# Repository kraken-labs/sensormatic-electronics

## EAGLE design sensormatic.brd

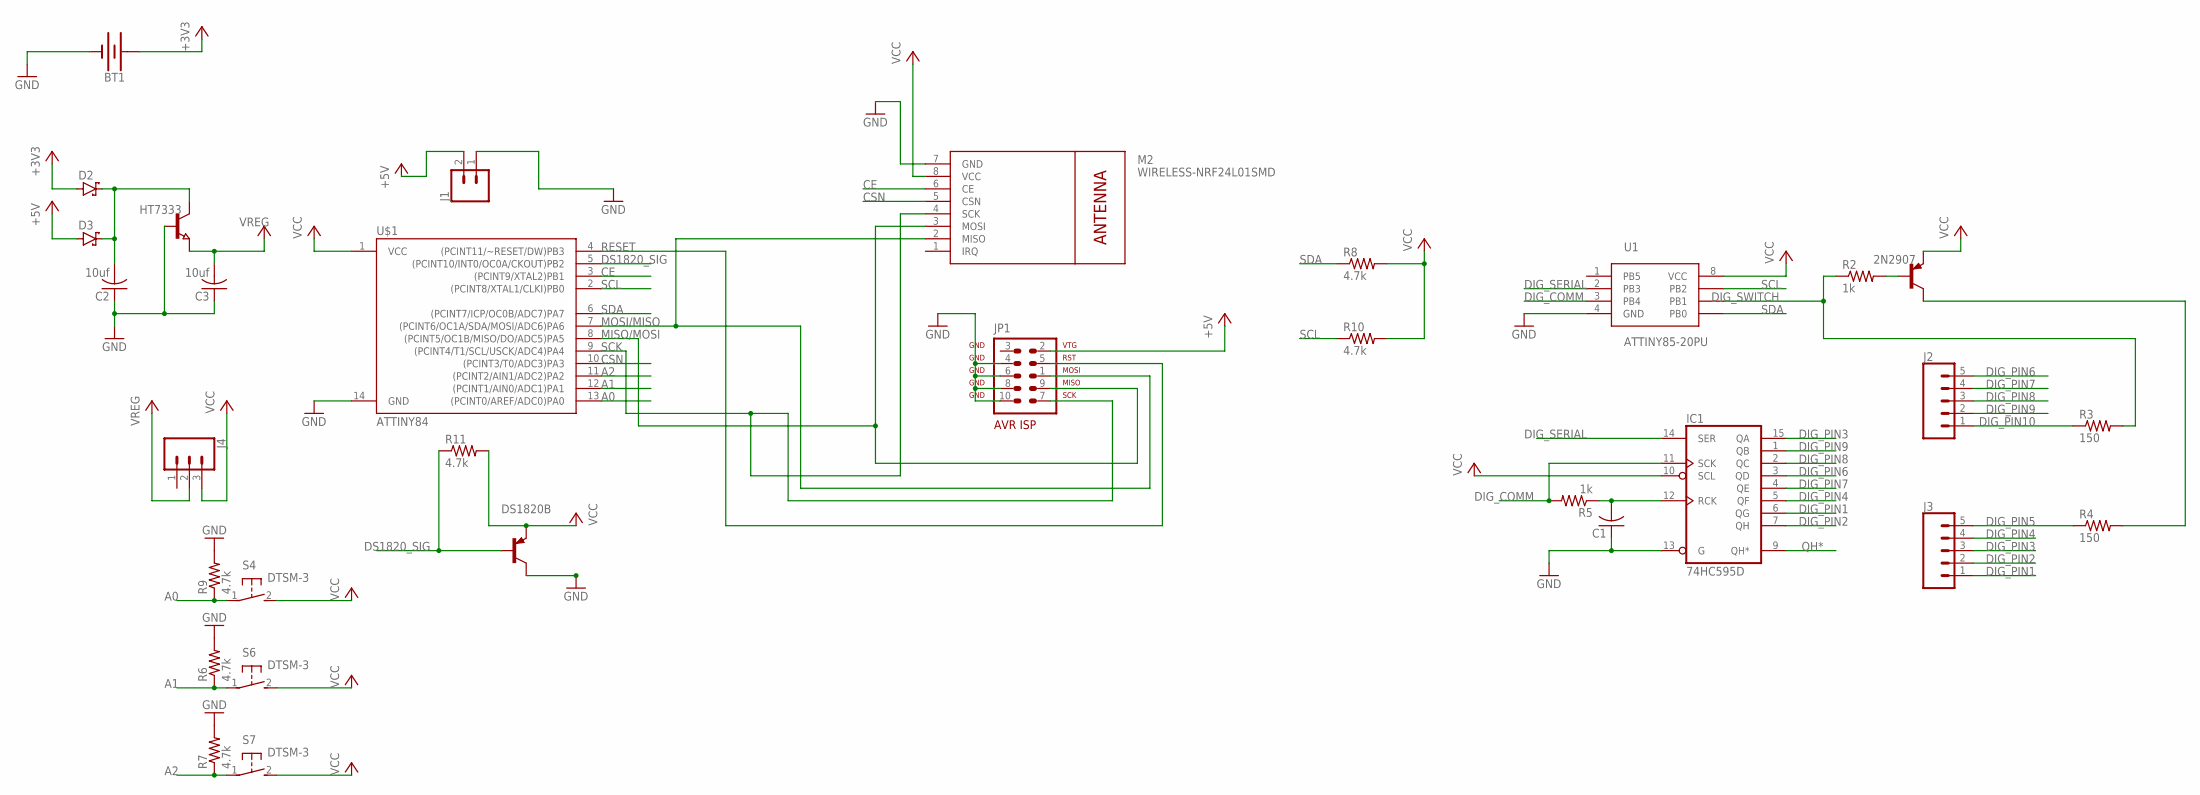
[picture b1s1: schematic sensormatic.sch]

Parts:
2N2907: BCX71SMD; SOT23
BT1: BATTERY-20MM_PTH; BATTCOM_20MM_PTH
C1: C-USC0603; C0603
C2, C3: 10uf; C0603
D2, D3: SCHOTTKY-DIODESMD; SMB
DS1820B: -PNP-TO92; TO92
HT7333: NPN-TRANSISTOR_SOT89; SOT89
IC1: 74HC595D; SO16
J1: CONN_02; 1X02
J2, J3: CONN_05NO_SILK; 1X05_NO_SILK
J4: CONN_03; 1X03
JP1: AVR-ISP-10
M2: WIRELESS-NRF24L01SMD; WIRELESS-NRF24L01-SMD
R2, R5: 1k; R0805
R3, R4: 150; R0805
R6, R7, R8, R9, R10, R11: 4.7k; R0805
S4, S6, S7: DTSM-3
U1: ATTINY85-20PU; PDIP-8
U$1: ATTINY84; SO14

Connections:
+3V3: BT1.1 (+), D2.A
+5V: D3.A, J1.2, JP1.2
A0: R9.1, S4.1, U$1.13 ((PCINT0/AREF/ADC0)PA0)
A1: R6.1, S6.1, U$1.12 ((PCINT1/AIN0/ADC1)PA1)
A2: R7.1, S7.1, U$1.11 ((PCINT2/AIN1/ADC2)PA2)
CE: M2.6 (CE), U$1.3 ((PCINT9/XTAL2)PB1)
CSN: M2.5 (CSN), U$1.10 ((PCINT3/T0/ADC3)PA3)
DIG_COMM: IC1.11 (SCK), R5.2, U1.3 (PB4)
DIG_PIN1: IC1.6 (QG), J3.1
DIG_PIN2: IC1.7 (QH), J3.2
DIG_PIN3: IC1.15 (QA), J3.3
DIG_PIN4: IC1.5 (QF), J3.4
DIG_PIN5: J3.5, R4.1
DIG_PIN6: IC1.3 (QD), J2.5
DIG_PIN7: IC1.4 (QE), J2.4
DIG_PIN8: IC1.2 (QC), J2.3
DIG_PIN9: IC1.1 (QB), J2.2
DIG_PIN10: J2.1, R3.1
DIG_SERIAL: IC1.14 (SER), U1.2 (PB3)
DIG_SWITCH: R2.1, R3.2, U1.6 (PB1)
DS1820_SIG: DS1820B.2 (B), R11.1, U$1.5 ((PCINT10/INT0/OC0A/CKOUT)PB2)
GND: BT1.2 (-), C1.1, C2.1, C3.1, DS1820B.3 (C), HT7333.1 (B), IC1.8 (GND), IC1.13 (G), J1.1, JP1.4, JP1.6, JP1.8, JP1.10, M2.7 (GND), R6.2, R7.2, R9.2, U1.4 (GND), U$1.14 (GND)
MISO/MOSI: JP1.9, M2.3 (MOSI), U$1.8 ((PCINT5/OC1B/MISO/DO/ADC5)PA5)
MOSI/MISO: JP1.1, M2.2 (MISO), U$1.7 ((PCINT6/OC1A/SDA/MOSI/ADC6)PA6)
unnamed: C2.2, D2.C, D3.C, HT7333.2 (C)
unnamed: 2N2907.1 (B), R2.2
unnamed: C1.2, IC1.12 (RCK), R5.1
unnamed: 2N2907.3 (C), R4.2
QH*: IC1.9 (QH*)
RESET: JP1.5, U$1.4 ((PCINT11/~RESET/DW)PB3)
SCK: JP1.7, M2.4 (SCK), U$1.9 ((PCINT4/T1/SCL/USCK/ADC4)PA4)
SCL: R10.1, U1.7 (PB2), U$1.2 ((PCINT8/XTAL1/CLKI)PB0)
SDA: R8.1, U1.5 (PB0), U$1.6 ((PCINT7/ICP/OC0B/ADC7)PA7)
VCC: 2N2907.2 (E), DS1820B.1 (E), IC1.10 (SCL), IC1.16 (VCC), J4.3, M2.8 (VCC), R8.2, R10.2, R11.2, S4.2, S6.2, S7.2, U1.8 (VCC), U$1.1 (VCC)
VREG: C3.2, HT7333.3 (E), J4.2

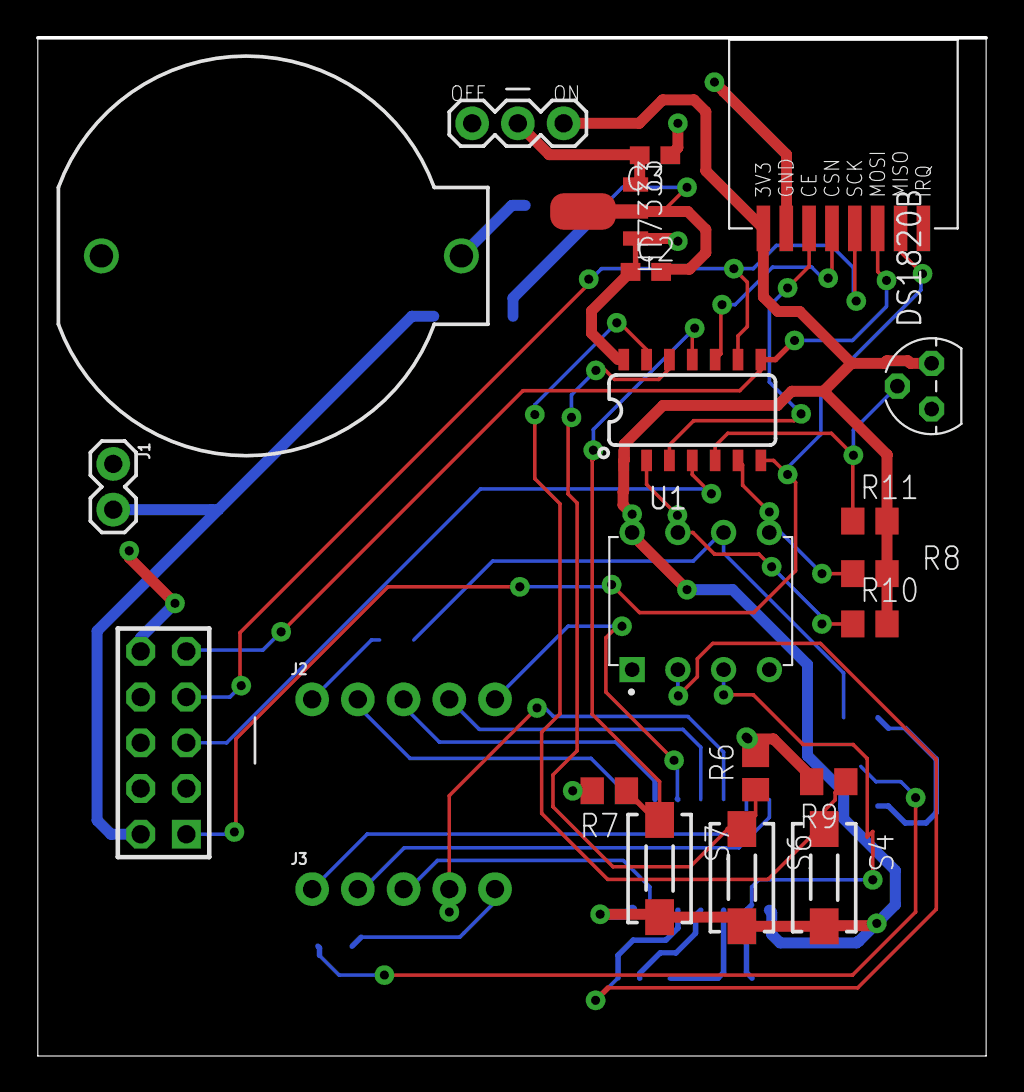
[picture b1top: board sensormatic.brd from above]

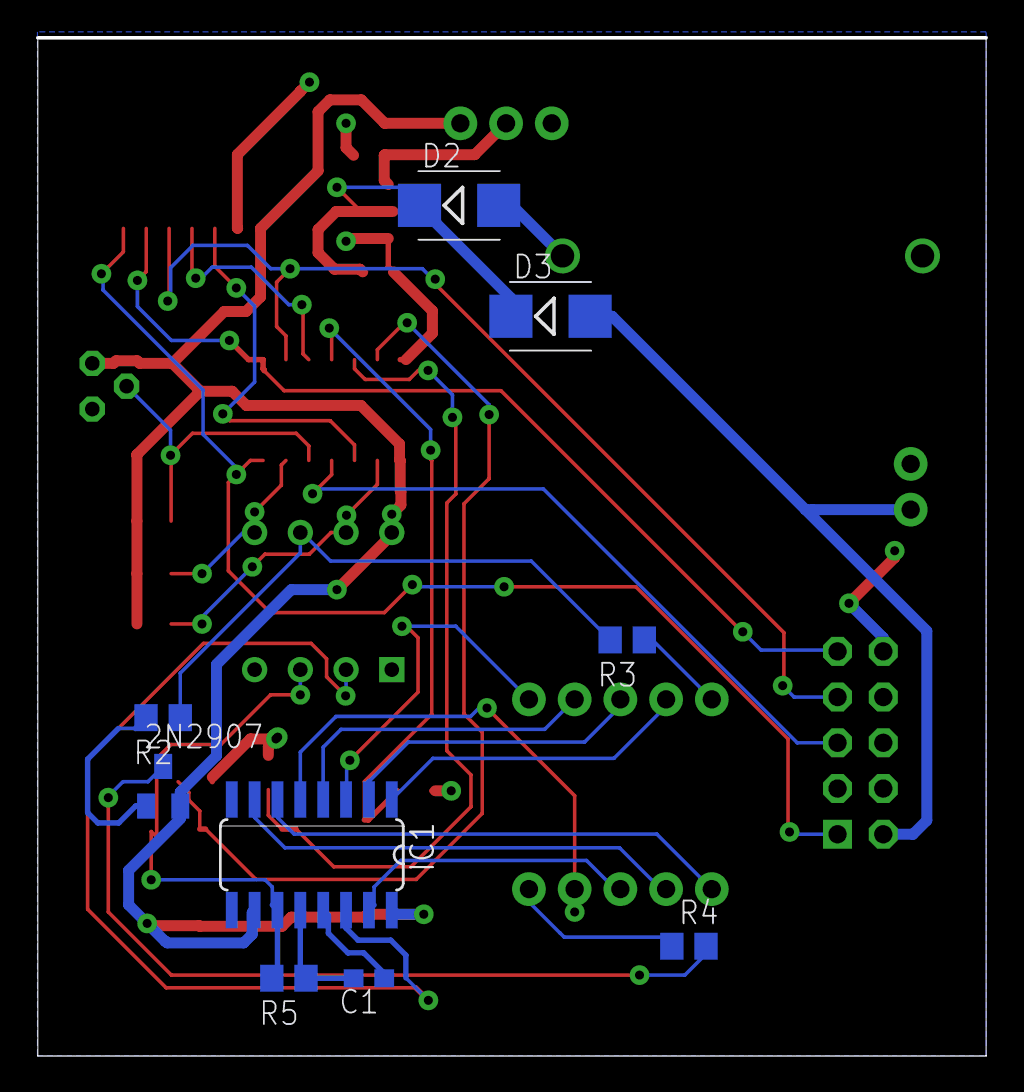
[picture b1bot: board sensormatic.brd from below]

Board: 2 copper layers, 52.7 x 56.5 mm, 31 parts (9 on the bottom side), 34 nets.

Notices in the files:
parts and their libraries:
SparkFun-IC-Microcontroller: Licensing: Creative Commons ShareAlike 4.0 International - https://creativecommons.org/licenses/by-sa/4.0
